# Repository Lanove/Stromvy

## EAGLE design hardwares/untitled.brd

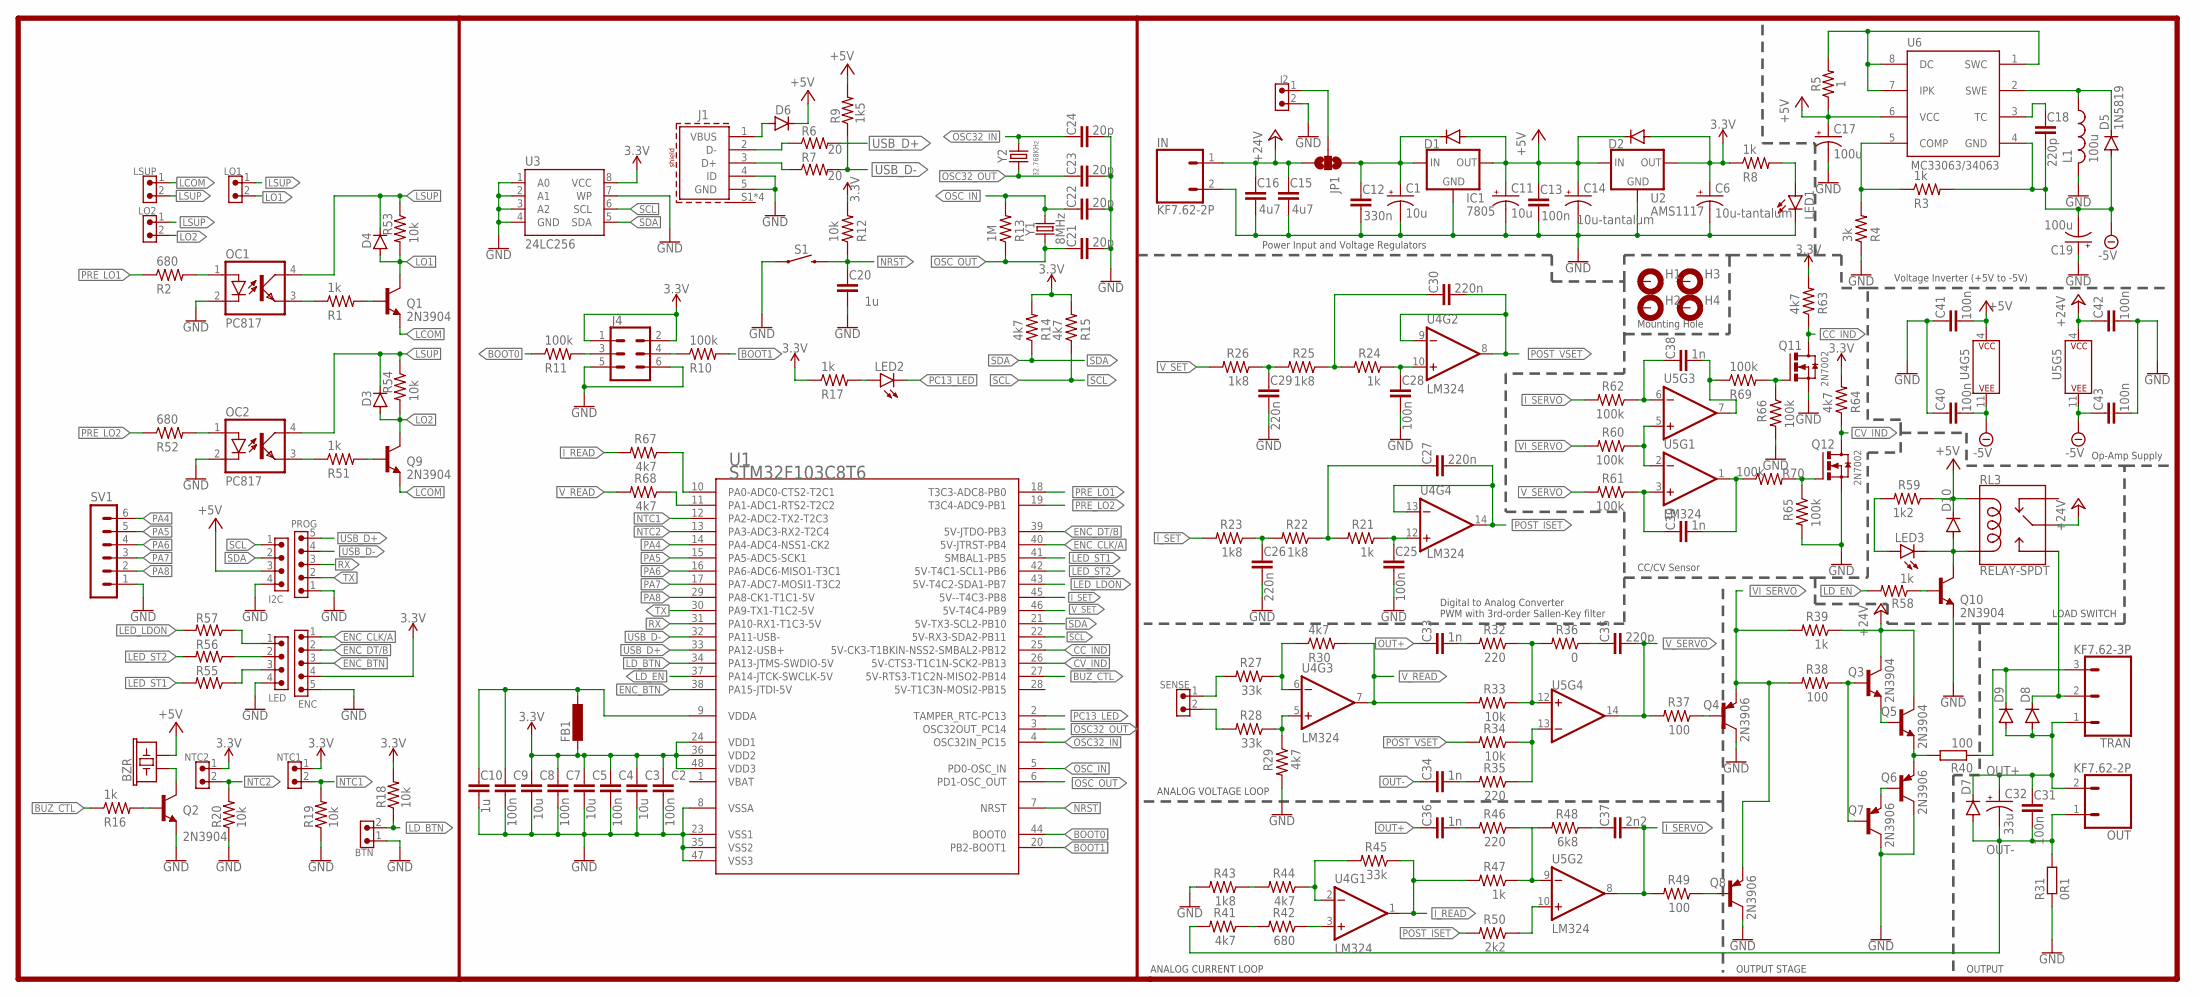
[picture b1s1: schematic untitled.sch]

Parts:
BTN: 61900211121
BZR: BUZZER-PTH_KIT; BUZZER-12MM-KIT
C1, C11: 10u; E2,5-6
C2, C4, C7, C9, C13, C25, C28, C31, C40, C41, C42, C43: 100n; C0805
C3, C5, C8: 10u; C0805
C6, C14: 10u-tantalum; CT3528
C10, C20: 1u; C0805
C12: 330n; C0805
C15, C16: 4u7; C0805
C17, C19: 100u; E2,5-6
C18, C35: 220p; C0805
C21, C22, C23, C24: 20p; C0805
C26, C27, C29, C30: 220n; C0805
C32: 33u; D/7343-31R
C33, C34, C36, C38, C39: 1n; C0805
C37: 2n2; C0805
D1, D2, D3, D4, D6, D7, D8, D9, D10: DIODE-DO-214AC; DO-214AC
D5: 1N5819; DO-214AC
ENC: 61900511121
FB1: L-EUL1812; L1812
H1, H2, H3, H4: MOUNT-PAD-ROUND3.2; 3,2-PAD
I2C: 61900411121
IC1: 7805; 78XXS
IN: KF7.62-2P; KF7.62
J1: 629105136821
J2: 61900211121
J4: FEMALE 2x3; 2X3
JP1: JUMPER-SMT_3_NO_NO-SILK; SMT-JUMPER_3_NO_NO-SILK
L1: 100u; 6000-XXXX-RC
LED: 61900411121
LED1, LED2, LED3: LEDCHIP-LED0805; CHIP-LED0805
LO1, LO2: 61900211121
LSUP: 61900211121
NTC1, NTC2: 61900211121
OC1, OC2: PC817; DIL04
OUT: KF7.62-2P; KF7.62
PROG: 61900511121
Q1, Q2, Q3, Q5, Q9, Q10: 2N3904; TO92
Q4, Q6, Q7, Q8: 2N3906; TO92
Q11, Q12: 2N7002; SOT23-3
R1, R3, R8, R16, R17, R21, R24, R39, R47, R51, R58: 1k; M0805
R2, R42, R52, R55, R56, R57: 680; M0805
R4: 3k; M0805
R5: 1; 2010
R6, R7: 20; M0805
R9: 1k5; M0805
R10, R11, R60, R61, R62, R65, R66, R69, R70: 100k; M0805
R12, R18, R19, R20, R33, R34, R53, R54: 10k; M0805
R13: 1M; M0805
R14, R15, R29, R30, R41, R44, R63, R64, R67, R68: 4k7; M0805
R22, R23, R25, R26, R43: 1k8; M0805
R27, R28, R45: 33k; M0805
R31: 0R1; 0922/22
R32, R35, R46: 220; M0805
R36: 0; M0805
R37, R38, R49: 100; M0805
R40: 100; 0922/22
R48: 6k8; M0805
R50: 2k2; M0805
R59: 1k2; M0805
RL3: RELAY-SPDT; RELAY_G5LE
S1: MOMENTARY-SWITCH-SPST-SMD-6.2MM-TALL; TACTILE_SWITCH_SMD_6.2MM_TALL
SENSE: 61900211121
SV1: MA06-1
TRAN: KF7.62-3P
U1: STM32F103C8T6; TQFP48
U2: AMS1117; SOT89R
U3: 24LC256; SO08
U4, U5: LM324; SO14
U6: 34063; SO08
Y1: 8MHz; HC49US
Y2: 32.768KHz; MC-306

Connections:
3.3V: C2.1, C3.1, C4.1, C5.1, C6.+, C7.1, C8.1, D2.A, ENC.4, FB1.2, J4.1, J4.2, NTC1.1, NTC2.1, R8.1, R12.2, R14.2, R15.2, R17.1, R18.2, R63.2, R64.2, U1.24 (VDD1), U1.36 (VDD2), U1.48 (VDD3), U2.3 (OUT), U2.4 (OUT), U3.8 (VCC)
+5V: BZR.- (2), C11.+, C13.1, C14.+, C17.+, C41.2, D1.A, D2.C, D6.C, D10.C, I2C.3, IC1.OUT, R5.1, R9.2, R59.1, RL3.2 (COIL1), U2.1 (IN), U4.4 (P$V+), U6.6 (VCC)
+24V: C15.1, C16.1, C42.1, IN.1, JP1.3, Q3.1 (C), Q5.1 (C), R39.1, RL3.1 (MAIN), U5.4 (P$V+)
-5V: C18.2, C19.-, C40.2, C43.1, D5.A, R3.2, U4.11 (P$V-), U5.11 (P$V-), U6.4 (GND)
BASE: D9.C, R40.1, TRAN.3
BOOT0: R11.1, U1.44 (BOOT0)
BOOT1: R10.2, U1.20 (PB2-BOOT1)
BUZ_CTL: R16.1, U1.27 (5V-RTS3-T1C2N-MISO2-PB14)
CC_IND: Q11.3 (D), R63.1, U1.25 (5V-CK3-T1BKIN-NSS2-SMBAL2-PB12)
COL: D8.C, RL3.3 (NO), TRAN.2
CV_IND: Q12.3 (D), R64.1, U1.26 (5V-CTS3-T1C1N-SCK2-PB13)
ENC_BTN: ENC.3, U1.38 (PA15-JTDI-5V)
ENC_CLK/A: ENC.1, U1.40 (5V-JTRST-PB4)
ENC_DT/B: ENC.2, U1.39 (5V-JTDO-PB3)
GND: BTN.1, C1.-, C2.2, C3.2, C4.2, C5.2, C6.-, C7.2, C8.2, C9.2, C10.2, C11.-, C12.2, C13.2, C14.-, C15.2, C16.2, C17.-, C19.+, C20.2, C21.2, C22.2, C23.2, C24.2, C25.2, C26.2, C28.2, C29.2, C40.1, C41.1, C42.2, C43.2, ENC.5, I2C.4, IC1.GND, IN.2, J1.4 (ID), J1.5 (GND), J2.2, J4.5, J4.6, L1.2, LED.4, LED1.C, OC1.2 (C), OC2.2 (C), PROG.1, Q2.3 (E), Q4.1 (C), Q6.1 (C), Q7.1 (C), Q8.1 (C), Q10.3 (E), Q11.2 (S), Q12.2 (S), R4.1, R19.1, R20.1, R29.2, R31.1, R43.2, R65.2, R66.2, S1.A2 (1), SV1.1, U1.8 (VSSA), U1.23 (VSS1), U1.35 (VSS2), U1.47 (VSS3), U2.2 (GND), U3.1 (A0), U3.2 (A1), U3.3 (A2), U3.4 (GND), U3.7 (WP)
I_READ: R45.1, R47.2, R67.2, U4.1 (OUT)
I_SERVO: C37.2, R49.2, R62.2, U5.8 (OUT)
I_SET: R23.2, U1.45 (5V--T4C3-PB8)
LCOM: LSUP.1, Q1.3 (E), Q9.3 (E)
LD_BTN: BTN.2, R18.1, U1.34 (PA13-JTMS-SWDIO-5V)
LD_EN: R58.2, U1.37 (PA14-JTCK-SWCLK-5V)
LED_LDON: R57.2, U1.43 (5V-T4C2-SDA1-PB7)
LED_ST1: R55.2, U1.41 (SMBAL1-PB5)
LED_ST2: R56.2, U1.42 (5V-T4C1-SCL1-PB6)
LO1: D4.A, LO1.2, Q1.1 (C), R53.2
LO2: D3.A, LO2.2, Q9.1 (C), R54.2
LSUP: D3.C, D4.C, LO1.1, LO2.1, LSUP.2, OC1.4 (COL), OC2.4 (COL), R53.1, R54.1
unnamed: C1.+, C12.1, D1.C, IC1.IN, JP1.1
unnamed: Q1.2 (B), R1.2
unnamed: J2.1, JP1.2
unnamed: LED1.A, R8.2
unnamed: OC1.3 (EMIT), R1.1
unnamed: D6.A, J1.1 (VBUS)
unnamed: Q9.2 (B), R51.2
unnamed: OC2.3 (EMIT), R51.1
unnamed: OC2.1 (A), R52.2
unnamed: OC1.1 (A), R2.2
unnamed: C9.1, C10.1, FB1.1, U1.9 (VDDA)
unnamed: C18.1, U6.3 (TC)
unnamed: D5.C, L1.1, U6.2 (SWE)
unnamed: R5.2, U6.1 (SWC), U6.7 (IPK), U6.8 (DC)
unnamed: J1.3 (D+), R7.1
unnamed: R3.1, R4.2, U6.5 (COMP)
unnamed: J1.2 (D-), R6.1
unnamed: J4.3, R11.2
unnamed: J4.4, R10.1
unnamed: Q2.2 (B), R16.2
unnamed: LED2.A, R17.2
unnamed: BZR.+ (1), Q2.1 (C)
unnamed: C28.1, R24.1, U4.10 (+IN)
unnamed: C29.1, R25.2, R26.1
unnamed: C30.1, R24.2, R25.1
unnamed: Q3.2 (B), Q7.2 (B), R38.1
unnamed: R27.1, R30.1, U4.6 (-IN)
unnamed: R28.1, R29.1, U4.5 (+IN)
unnamed: C25.1, R21.1, U4.12 (+IN)
unnamed: C27.1, R21.2, R22.1
unnamed: C26.1, R22.2, R23.1
unnamed: Q6.2 (B), Q7.3 (E)
unnamed: R68.1, U1.11 (PA1-ADC1-RTS2-T2C2)
unnamed: R32.1, R33.1, R36.2, U5.12 (+IN)
unnamed: LED.1, R57.1
unnamed: C33.2, R32.2
unnamed: Q5.3 (E), Q6.3 (E), R40.2
unnamed: Q3.3 (E), Q5.2 (B)
unnamed: C35.1, R36.1
unnamed: R67.1, U1.10 (PA0-ADC0-CTS2-T2C1)
unnamed: C34.2, R35.2
unnamed: R34.1, R35.1, U5.13 (-IN)
unnamed: Q4.2 (B), R37.1
unnamed: Q12.1 (G), R65.1, R70.2
unnamed: R41.1, R42.2
unnamed: R42.1, U4.3 (+IN)
unnamed: R44.1, R45.2, U4.2 (-IN)
unnamed: R43.1, R44.2
unnamed: Q11.1 (G), R66.1, R69.2
unnamed: C38.2, R69.1, U5.7 (OUT)
unnamed: C36.2, R46.2
unnamed: R46.1, R47.1, R48.2, U5.9 (-IN)
unnamed: C37.1, R48.1
unnamed: R50.1, U5.10 (+IN)
unnamed: Q8.2 (B), R49.1
unnamed: LED.2, R56.1
unnamed: LED.3, R55.1
unnamed: D10.A, LED3.C, Q10.1 (C), RL3.5 (COIL2)
unnamed: R60.1, U5.2 (-IN), U5.5 (+IN)
unnamed: Q10.2 (B), R58.1
unnamed: LED3.A, R59.2
unnamed: C39.1, R61.1, U5.3 (+IN)
unnamed: C39.2, R70.1, U5.1 (OUT)
unnamed: C38.1, R62.1, U5.6 (-IN)
NRST: C20.1, R12.1, S1.B2 (2), U1.7 (NRST)
NTC1: NTC1.2, R19.2, U1.12 (PA2-ADC2-TX2-T2C3)
NTC2: NTC2.2, R20.2, U1.13 (PA3-ADC3-RX2-T2C4)
OSC32_IN: C24.1, U1.4 (OSC32IN_PC15), Y2.4 (2)
OSC32_OUT: C23.1, U1.3 (OSC32OUT_PC14), Y2.1
OSC_IN: C22.1, R13.2, U1.5 (PD0-OSC_IN), Y1.2
OSC_OUT: C21.1, R13.1, U1.6 (PD1-OSC_OUT), Y1.1
OUT+: C31.1, C32.+, C33.1, C36.1, D7.C, D8.A, D9.A, OUT.2, TRAN.1
OUT-: C31.2, C32.-, C34.1, D7.A, OUT.1, R31.2, R41.2
PA4: SV1.6, U1.14 (PA4-ADC4-NSS1-CK2)
PA5: SV1.5, U1.15 (PA5-ADC5-SCK1)
PA6: SV1.4, U1.16 (PA6-ADC6-MISO1-T3C1)
PA7: SV1.3, U1.17 (PA7-ADC7-MOSI1-T3C2)
PA8: SV1.2, U1.29 (PA8-CK1-T1C1-5V)
PC13_LED: LED2.C, U1.2 (TAMPER_RTC-PC13)
POST_ISET: C27.2, R50.2, U4.13 (-IN), U4.14 (OUT)
POST_VSET: C30.2, R34.2, U4.8 (OUT), U4.9 (-IN)
PRE_LO1: R2.1, U1.18 (T3C3-ADC8-PB0)
PRE_LO2: R52.1, U1.19 (T3C4-ADC9-PB1)
RX: PROG.3, U1.31 (PA10-RX1-T1C3-5V)
SCL: I2C.1, R15.1, U1.22 (5V-RX3-SDA2-PB11), U3.6 (SCL)
SDA: I2C.2, R14.1, U1.21 (5V-TX3-SCL2-PB10), U3.5 (SDA)
SENSE+: R28.2, SENSE.2
SENSE-: R27.2, SENSE.1
TX: PROG.2, U1.30 (PA9-TX1-T1C2-5V)
USB_D+: PROG.5, R6.2, U1.33 (PA12-USB+)
USB_D-: PROG.4, R7.2, R9.1, U1.32 (PA11-USB-)
VBAT: U1.1 (VBAT)
VI_SERVO: Q4.3 (E), Q8.3 (E), R38.2, R39.2, R60.2
V_READ: R30.2, R33.2, R68.2, U4.7 (OUT)
V_SERVO: C35.2, R37.2, R61.2, U5.14 (OUT)
V_SET: R26.2, U1.46 (5V-T4C4-PB9)

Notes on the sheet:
Digital to Analog Converter PWM with 3rd-order Sallen-Key filter
CC/CV Sensor
Mounting Hole
Op-Amp Supply
Voltage Inverter (+5V to -5V)
Power Input and Voltage Regulators
ANALOG VOLTAGE LOOP
ANALOG CURRENT LOOP
OUTPUT STAGE
LOAD SWITCH
OUTPUT

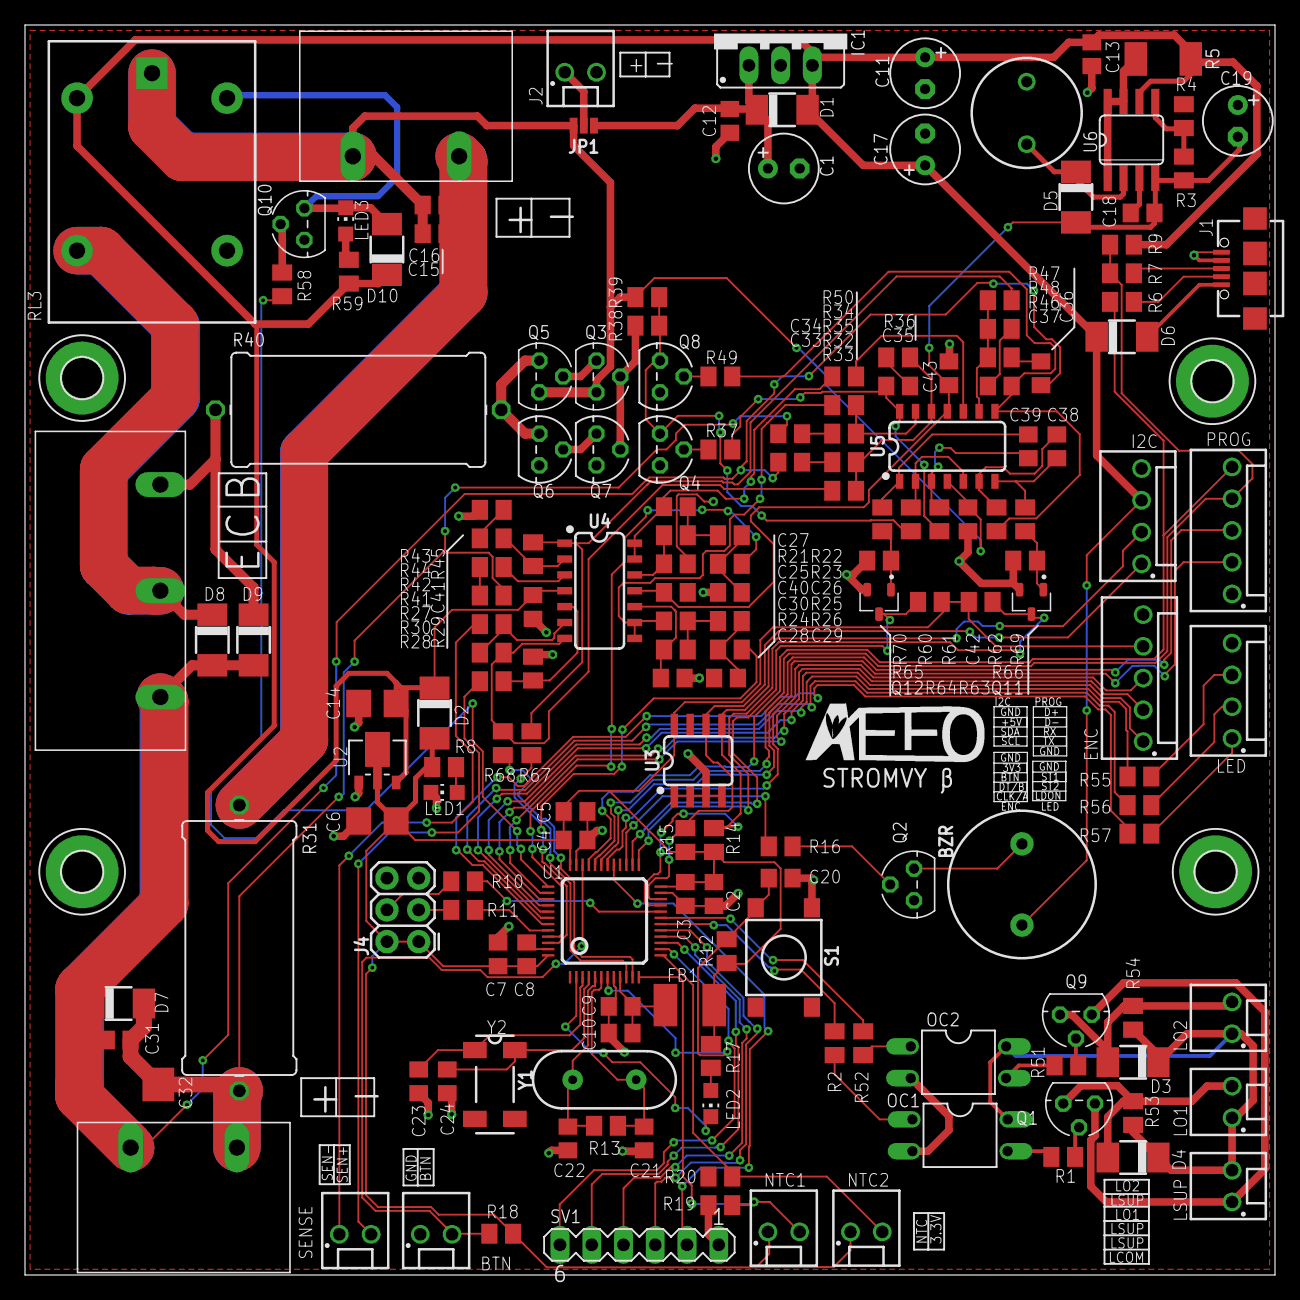
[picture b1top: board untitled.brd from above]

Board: 2 copper layers, 100.0 x 100.0 mm, 177 parts (0 on the bottom side), 122 nets.

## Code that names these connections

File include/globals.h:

#include <Arduino.h>
#include <encoderController.h>
#include <lcdController.h>
#include <eepromController.h>
#include <indicatorController.h>
#include <Wire.h>
#include <ClickEncoder.h>
#include <Eeprom24C04_16.h>
#include "stm32f1xx_hal.h"
#include <RunningAverage.h>
#include "ADS1X15.h"
#include <IWatchdog.h>
#include <malloc.h>

#define WATCHDOG_TIMEOUT 6000000     // in uS (6s)
#define I2C_REFRESH_INTERVAL 1800000 // in ms (30m)

#define PIN_DEFINE // DO NOT DELETE

#define MODE_CC 0 // Used for opMode
#define MODE_CV 1 // Used for opMode

#define STATUS_ON 1  // Used for ldStatus
#define STATUS_OFF 0 // Used for ldStatus

#define ADS1115_ADDRESS 0x4A

#define OVERHEAT_TEMPERATURE 65 // maximum temperature for BJT to shutdown and goes OVERHEAT_HALT
#define LO2_MIN_CURRENT 0.0     // minimum current load for LO2 pwm map
#define LO2_MAX_CURRENT 2000.0  // maximum current load for LO2 pwm map

#define DAC_UPDATE_INTERVAL 10           // setCaptureCompare call interval, in msf
#define DAC_VOLTAGE_BASE_FACTOR 0.004619 // DAC to real voltage factor
#define DAC_CURRENT_BASE_FACTOR 1.095    // DAC to real current factor
#define DAC_CURRENT_OFFSET 19            // in mA

#define ADC_VOLTAGE_CHANNEL 0             // ADS1115 channel that is used to sense load voltage
#define ADC_CURRENT_CHANNEL 1             // ADS1115 channel that is used to sense load current
#define ADC_SAMPLE_INTERVAL 50            // ADC sample interval (also used for fan and energy)
#define ADC_SAMPLE_COUNT 20               // ADC running average total sample count (the bigger the value, the smoother the display but slower)
#define ADC_VOLTAGE_BASE_FACTOR 4.7299732 // Sensed voltage to real voltage factor
#define ADC_LSB_TO_CURRENT_MA 0.201560928 // ADC-LSB to real current
#define ADC_CURRENT_OFFSET 80             // ADC binary offset to cancel negative values

#define NTC_R1 10000.0         // The R1 of voltage divider for NTC
#define NTC_c1 1.009249522e-03 //c1 constant
#define NTC_c2 2.378405444e-04 //c2 constant
#define NTC_c3 2.019202697e-07 //c3 constant

#define MAX_V_DAC 4330 // Maximum DAC binary value (~20V)
#define MAX_I_DAC 2800 // Maximum DAC binary value (~3000mA)
#define MIN_V_DAC 100  // Minimum DAC binary value (~0.5V)
#define MIN_I_DAC 0    // Minimum DAC binary value (~19mA)

#define MAX_TIMER_DURATION 36000000 // in ms, 36000000 = 10 Hour
#define MIN_TIMER_DURATION 0
#define MAX_LOG_INTERVAL 60000 // in ms, 60000 = 1 Minute
#define MIN_LOG_INTERVAL 200   // in ms, 200 = 0.2 Second

#define MIN_FAN_PWM 0   // The absolute minimum for PWM value of fans
#define MAX_FAN_PWM 100 // The absolute maximum for PWM value of fans

#define MIN_FAN_TEMP 0  // The absolute minimum for bjt temperature for fan pwm map
#define MAX_FAN_TEMP 99 // The absolute maximum bjt temperature for fan pwm map

#define MAX_CALIBRATION_FACTOR 10.0000 // Self-explanatory
#define MIN_CALIBRATION_FACTOR 0.0001  // Self-explanatory

#define TIM4_ENCODER_PRESCALER 5 // prescaler for encoder routine call
#define TIM4_DAC_PRESCALER 2     // prescaler for dac increment/decrement routine call

#define LOGIC_OUTPUT1_TIMER_CHANNEL 3 // Timer channel used for LO1 associated with hardware pin (PB0 is T3C3)
#define LOGIC_OUTPUT2_TIMER_CHANNEL 4 // Timer channel used for LO2 associated with hardware pin (PB1 is T3C4)

#define I_SET_TIMER_CHANNEL 3 // Timer channel used for current adjustment associated with hardware pin (PB8 is T4C3)
#define V_SET_TIMER_CHANNEL 4 // Timer channel used for current adjustment associated with hardware pin (PB8 is T4C4)

#ifdef PIN_DEFINE

#define LED_PC13 PC13

#define ENC_CLK PB4
#define ENC_DT PB3
#define ENC_BTN PA15
#define ENC_STEPS 4

#define LCD_SDA PB11
#define LCD_SCL PB10

#define BUZZER_PIN PB14

#define LD_BTN PA13
#define LD_EN PA14

#define LOGIC_OUTPUT1 PB0
#define LOGIC_OUTPUT2 PB1

#define NTC1 PA2
#define NTC2 PA3

#define CC_IND PB12
#define CV_IND PB13

#define I_SET PB8
#define V_SET PB9
#endif

extern int presetVoltageDAC, // Variable to store digital value (0~5000) of preset voltage
    presetCurrentDAC;        // Variable to store digital value (0~5000) of preset current
// SCREEN_MAIN VARIABLES
extern float sensedVoltage, // variable to store real sensed voltage on terminal, used on main and lcdController
    sensedCurrent,          // variable to store real sensed current flow to load, used on main and lcdController
    sensedPower,            // variable to store real power dissipated by load, used on main and lcdController
    presetVoltage,          // The preset value of real voltage
    presetCurrent,          // The preset value of real current
    bjtTemp;                // The measured temperature of the output BJT
extern bool ldStatus,       // Load status, whether it's ON or OFF
    opMode,                 // Current operation of Power supply which is CC or CV
    timerStatus;            // Timer status, whether it's ON or OFF
// SCREEN_MENU VARIABLES
extern uint32_t timerDuration; // variable to store timer duration that user intended, if value is 0 then timer is OFF
// SCREEN_ENERGY VARIABLES
extern float mWhTotal,       // Total energy used by load in mWh
    mAhTotal;                // Total energy used by load in mAh
extern uint32_t timeRunning; // variable to keep track total time running, recorded when ldStatus is ON and paused when ldStatus is OFF
// SCREEN_LOG VARIABLES
extern uint32_t logInterval; // The interval logging value spit out on UART port
extern bool logStatus;       // the status of logging, enabled or disable
// SCREEN_FAN VARIABLES
extern int8_t minPWMLO1, // EEPROM address 0. Stored on EEPROM on save, minimum PWM value for logic output 1
    maxPWMLO1,           // EEPROM address 1. Stored on EEPROM on save, maximum PWM value for logic output 1
    minPWMLO2,           // EEPROM address 2. Stored on EEPROM on save, minimum PWM value for logic output 2
    maxPWMLO2;           // EEPROM address 3. Stored on EEPROM on save, maximum PWM value for logic output 2
extern float maxTemp,    // EEPROM address 4. Stored on EEPROM on save, maximum temperature for logic output (logic output will put out maximum PWM value if temperature is higher or equal maxTemp)
    minTemp;             // EEPROM address 8. Stored on EEPROM on save, minimum temperature for logic output (logic output will put out minimum PWM value if temperature is lower or equal to minTemp)
// SCREEN_CAL VARIABLES
extern float presetVoltageFactor, // EEPROM address 12. Stored on EEPROM on save, preset voltage will be multiplied by this factor before shown on LCD
    presetCurrentFactor,          // EEPROM address 16. Stored on EEPROM on save, preset current will be multiplied by this factor before shown on LCD
    sensedCurrentFactor,          // EEPROM address 20. Stored on EEPROM on save, sensed voltage will be multiplied by this factor before shown on LCD
    sensedVoltageFactor;          // EEPROM address 24. Stored on EEPROM on save, sensed voltage will be multiplied by this factor before shown on LCD
extern uint16_t adcTimeoutCounter;

extern unsigned long usedHeap, usedStack, usedPgm, freeRAM, highestHeapUsage;

extern "C" char *sbrk(int i);
/* Use linker definition */
extern char _end;
extern char _sdata;
extern char _estack;
extern char _Min_Stack_Size;

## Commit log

2021-08-02 init
2021-08-02 Added eeprom and lcd interfacing
2021-08-06 added HAL GPIO and ADC Init, and HAL adcRead
2021-08-06 change V and I ADC to external ADS1115, added RunningAverage
2021-08-06 specify RunningAverage type (int16_t)
2021-08-11 added lcdController and encoderController
2021-08-14 Added setScreen() functionality (WIP)
2021-08-15 lcdController done (untested) added encoderController
2021-08-15 lcdController and encoderController work Added navigations
2021-08-17 Added PSU Basic Functionality Changed variables constrain method
2021-08-19 fixed encoder acceleration problem by adding 1ms interrupt
2021-08-19 Added eepromControllerClass bugfix sensed voltage on cal screen not updating
2021-08-19 minor bugfix : presetCurrent does'nt update EEPROM changed EEPROM update method to every double click
2021-08-19 added load button functionality DAC /dec 7.7kHz when ldStatus first on
2021-08-19 added overheat handler added fan handler added power sensing tested 50W transistor dissipation
2021-08-19 added energy info functionality and minor bugfix for lcd
2021-08-19 added timer and logging functionality
2021-08-20 Added indicatorController and complete implementation
2021-08-20 change LCD_REFRESH_INTERVAL to 200ms
2021-08-20 Added hardware files
2021-08-23 Modified encoder acceleration timer to better move on slower speed. Modified CC/CV Buzzer to not overlap. Fixed actual power lcd to not display negative value Changed current ADC offset to 80. Added 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
2021-08-25 UNTESTED Added commentary and minor code factor
2021-08-28 Added watchdog capability with 4 second timeout Use original and newest ver of running average lib (v0.4.0) Fixed sensedPower on LCD to not display negative sign
2021-08-29 Added modification list Added deconstructor for each controllerClass RunningAverage now average real voltage (float) instead of the ADC value (int16_t) Added memory debug function (unused)
2021-09-02 Added i2c refresh routine (every 5 min or ldButton dbclick)
2021-09-04 Changed watchdog time out to 6s Changed i2c refresh interval to 30m I2C refresh now reset watchdog timer aswell Added ADC reading timeout counter and measure Added LCD debug screen
2021-09-04 Use object instead of pointer to class for lcd,encoder,eeprom,timer, and running average fix running average maximum size to 20 (no malloc)
2021-09-04 Added memory debug lcd screen Added empty eeprom initialization Added highest heap usage record to eeprom
2021-09-04 Added SCREEN_DEBUG refresh functionality display_mallinfo() when ldButton released after hold

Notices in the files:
parts and their libraries:
Wurth_Connectors_WR-WTB: Copyright: Würth Elektronik
SparkFun-Electromechanical: Licensing: Creative Commons ShareAlike 4.0 International - https://creativecommons.org/licenses/by-sa/4.0
